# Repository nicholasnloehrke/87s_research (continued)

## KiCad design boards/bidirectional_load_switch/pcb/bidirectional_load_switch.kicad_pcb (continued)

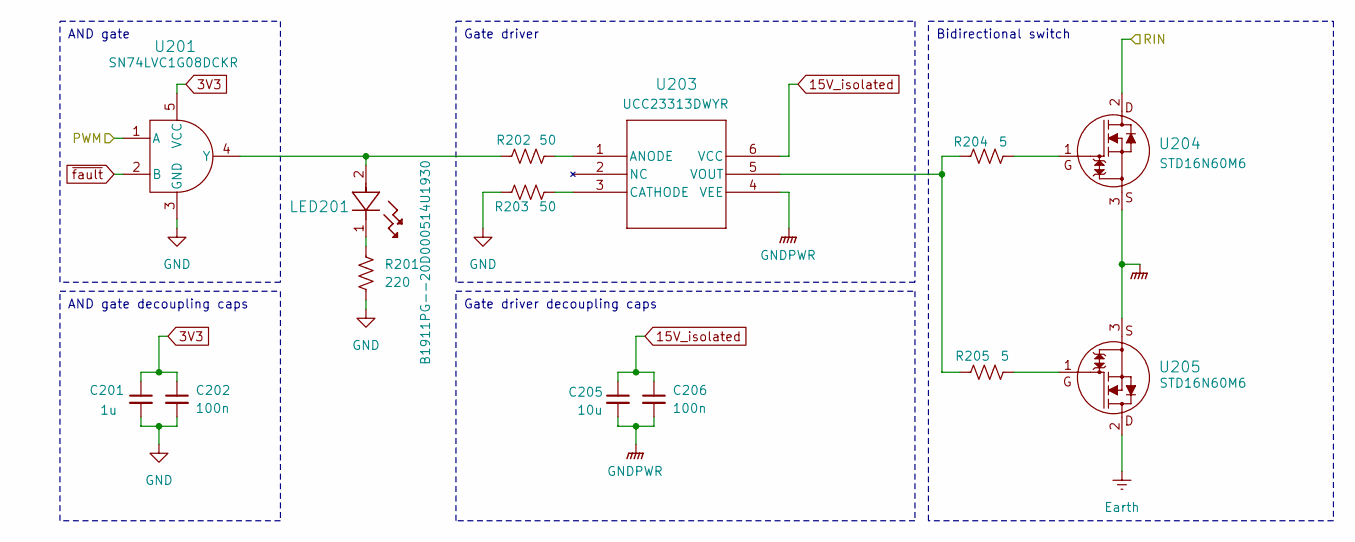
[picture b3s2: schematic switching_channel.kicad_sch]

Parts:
C201: 1u; C_0603_1608Metric
C202, C206: 100n; C_0603_1608Metric
C205: 10u; C_1206_3216Metric
LED201: LED_B1911PG--20D000514U1930_HVK; MPN B1911PG--20D000514U1930
R201: 220; R_0603_1608Metric
R202, R203: 50; R_0603_1608Metric
R204, R205: 5; R_0805_2012Metric
U201: DCK5; MPN SN74LVC1G08DCKR
U203: SOIC6_DWY_TEX; MPN UCC23313DWYR
U204, U205: DPAKTO-252_STM; MPN STD16N60M6

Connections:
3V3: C201.1, C202.1, U201.5 (VCC); also elsewhere on the board
15V_isolated: C205.1, C206.1, U203.6 (VCC); also elsewhere on the board
/Channel 1/RIN: U204.2; also elsewhere on the board
Earth: U205.2; also elsewhere on the board
GND: C201.2, C202.2, R201.2, R203.1, U201.3 (GND); also elsewhere on the board
GNDPWR: C205.2, C206.2, U203.4 (VEE), U204.3, U205.3; also elsewhere on the board
unnamed: LED201.1, R201.1
unnamed: R204.2, U204.1
unnamed: R205.2, U205.1
unnamed: LED201.2, R202.1, U201.4 (Y)
unnamed: R202.2, U203.1 (ANODE)
unnamed: R203.2, U203.3 (CATHODE)
unnamed: R204.1, R205.1, U203.5 (VOUT)
PWM1_in: U201.1 (A); also elsewhere on the board
~fault: U201.2 (B); also elsewhere on the board

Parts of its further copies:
C301, C401, C501, C601, C701, C801, C901: 1u; C_0603_1608Metric
C302, C306, C402, C406, C502, C506, C602, C606, C702, C706, C802, C806, C902, C906: 100n; C_0603_1608Metric
C305, C405, C505, C605, C705, C805, C905: 10u; C_1206_3216Metric
LED301, LED401, LED501, LED601, LED701, LED801, LED901: LED_B1911PG--20D000514U1930_HVK; MPN B1911PG--20D000514U1930
R301, R401, R501, R601, R701, R801, R901: 220; R_0603_1608Metric
R302, R303, R402, R403, R502, R503, R602, R603, R702, R703, R802, R803, R902, R903: 50; R_0603_1608Metric
R304, R305, R404, R405, R504, R505, R604, R605, R704, R705, R804, R805, R904, R905: 5; R_0805_2012Metric
U301, U401, U501, U601, U701, U801, U901: DCK5; MPN SN74LVC1G08DCKR
U303, U403, U503, U603, U703, U803, U903: SOIC6_DWY_TEX; MPN UCC23313DWYR
U304, U305, U404, U405, U504, U505, U604, U605, U704, U705, U804, U805, U904, U905: DPAKTO-252_STM; MPN STD16N60M6

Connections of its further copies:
3V3: C301.1, C302.1, C401.1, C402.1, C501.1, C502.1, C601.1, C602.1, C701.1, C702.1, C801.1, C802.1, C901.1, C902.1, U301.5 (VCC), U401.5 (VCC), U501.5 (VCC), U601.5 (VCC), U701.5 (VCC), U801.5 (VCC), U901.5 (VCC); also elsewhere on the board
15V_isolated: C305.1, C306.1, C405.1, C406.1, C505.1, C506.1, C605.1, C606.1, C705.1, C706.1, C805.1, C806.1, C905.1, C906.1, U303.6 (VCC), U403.6 (VCC), U503.6 (VCC), U603.6 (VCC), U703.6 (VCC), U803.6 (VCC), U903.6 (VCC); also elsewhere on the board
/Channel 2/RIN: U304.2; also elsewhere on the board
/Channel 3/RIN: U404.2; also elsewhere on the board
/Channel 4/RIN: U504.2; also elsewhere on the board
/Channel 5/RIN: U604.2; also elsewhere on the board
/Channel 6/RIN: U704.2; also elsewhere on the board
/Channel 7/RIN: U804.2; also elsewhere on the board
/Channel 8/RIN: U904.2; also elsewhere on the board
Earth: U305.2, U405.2, U505.2, U605.2, U705.2, U805.2, U905.2; also elsewhere on the board
GND: C301.2, C302.2, C401.2, C402.2, C501.2, C502.2, C601.2, C602.2, C701.2, C702.2, C801.2, C802.2, C901.2, C902.2, R301.2, R303.1, R401.2, R403.1, R501.2, R503.1, R601.2, R603.1, R701.2, R703.1, R801.2, R803.1, R901.2, R903.1, U301.3 (GND), U401.3 (GND), U501.3 (GND), U601.3 (GND), U701.3 (GND), U801.3 (GND), U901.3 (GND); also elsewhere on the board
GNDPWR: C305.2, C306.2, C405.2, C406.2, C505.2, C506.2, C605.2, C606.2, C705.2, C706.2, C805.2, C806.2, C905.2, C906.2, U303.4 (VEE), U304.3, U305.3, U403.4 (VEE), U404.3, U405.3, U503.4 (VEE), U504.3, U505.3, U603.4 (VEE), U604.3, U605.3, U703.4 (VEE), U704.3, U705.3, U803.4 (VEE), U804.3, U805.3, U903.4 (VEE), U904.3, U905.3; also elsewhere on the board
unnamed: LED301.1, R301.1
unnamed: LED401.1, R401.1
unnamed: LED501.1, R501.1
unnamed: LED601.1, R601.1
unnamed: LED701.1, R701.1
unnamed: LED801.1, R801.1
unnamed: LED901.1, R901.1
unnamed: R304.2, U304.1
unnamed: R305.2, U305.1
unnamed: R404.2, U404.1
unnamed: R405.2, U405.1
unnamed: R504.2, U504.1
unnamed: R505.2, U505.1
unnamed: R604.2, U604.1
unnamed: R605.2, U605.1
unnamed: R704.2, U704.1
unnamed: R705.2, U705.1
unnamed: R804.2, U804.1
unnamed: R805.2, U805.1
unnamed: R904.2, U904.1
unnamed: R905.2, U905.1
unnamed: LED301.2, R302.1, U301.4 (Y)
unnamed: R302.2, U303.1 (ANODE)
unnamed: R303.2, U303.3 (CATHODE)
unnamed: R304.1, R305.1, U303.5 (VOUT)
unnamed: LED401.2, R402.1, U401.4 (Y)
unnamed: R402.2, U403.1 (ANODE)
unnamed: R403.2, U403.3 (CATHODE)
unnamed: R404.1, R405.1, U403.5 (VOUT)
unnamed: LED501.2, R502.1, U501.4 (Y)
unnamed: R502.2, U503.1 (ANODE)
unnamed: R503.2, U503.3 (CATHODE)
unnamed: R504.1, R505.1, U503.5 (VOUT)
unnamed: LED601.2, R602.1, U601.4 (Y)
unnamed: R602.2, U603.1 (ANODE)
unnamed: R603.2, U603.3 (CATHODE)
unnamed: R604.1, R605.1, U603.5 (VOUT)
unnamed: LED701.2, R702.1, U701.4 (Y)
unnamed: R702.2, U703.1 (ANODE)
unnamed: R703.2, U703.3 (CATHODE)
unnamed: R704.1, R705.1, U703.5 (VOUT)
unnamed: LED801.2, R802.1, U801.4 (Y)
unnamed: R802.2, U803.1 (ANODE)
unnamed: R803.2, U803.3 (CATHODE)
unnamed: R804.1, R805.1, U803.5 (VOUT)
unnamed: LED901.2, R902.1, U901.4 (Y)
unnamed: R902.2, U903.1 (ANODE)
unnamed: R903.2, U903.3 (CATHODE)
unnamed: R904.1, R905.1, U903.5 (VOUT)
PWM2_in: U301.1 (A); also elsewhere on the board
PWM3_in: U401.1 (A); also elsewhere on the board
PWM4_in: U501.1 (A); also elsewhere on the board
PWM5_in: U601.1 (A); also elsewhere on the board
PWM6_in: U701.1 (A); also elsewhere on the board
PWM7_in: U801.1 (A); also elsewhere on the board
PWM8_in: U901.1 (A); also elsewhere on the board
~fault: U301.2 (B), U401.2 (B), U501.2 (B), U601.2 (B), U701.2 (B), U801.2 (B), U901.2 (B); also elsewhere on the board

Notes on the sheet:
Gate driver
Bidirectional switch
Gate driver decoupling caps
AND gate decoupling caps
AND gate

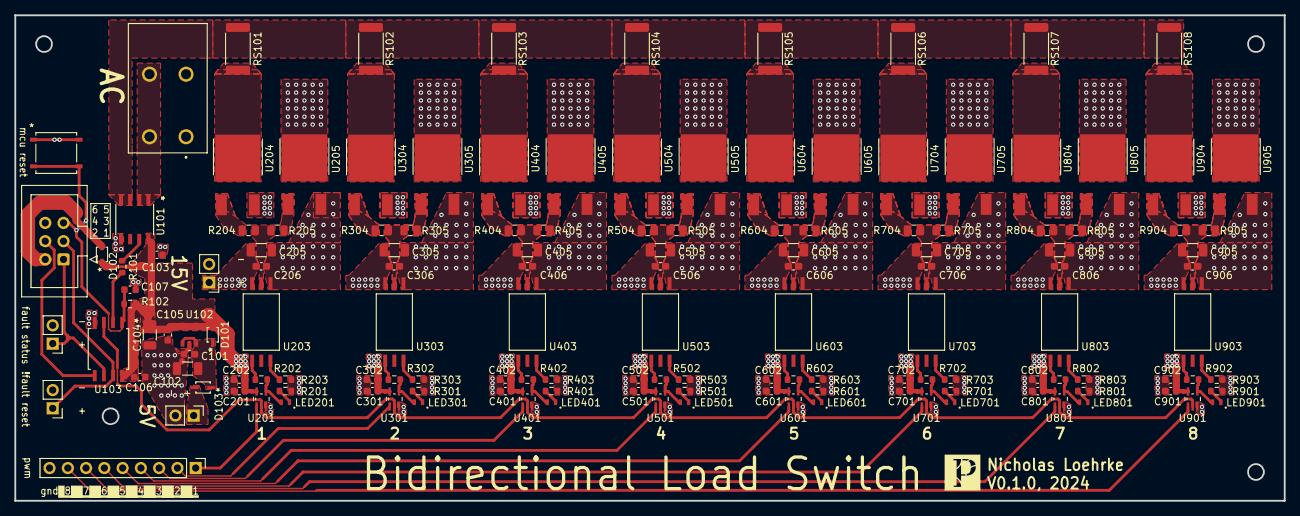
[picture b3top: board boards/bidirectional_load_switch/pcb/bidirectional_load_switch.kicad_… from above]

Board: 2 copper layers, 176.5 x 67.5 mm, 143 parts (0 on the bottom side), 89 nets.

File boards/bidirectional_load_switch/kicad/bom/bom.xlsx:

Reference | Value | Datasheet | Footprint | Qty | MPN
C101,C103,C105,C106,C107,C202,C206,C302,C306,C402,C406,C502,C506,C602,C606,C702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 | 100n | ~ | Capacitor_SMD:C_0603_1608Metric | 21
C102,C104,C205,C305,C405,C505,C605,C705,C805,C905 | 10u | ~ | Capacitor_SMD:C_1206_3216Metric | 10
C201,C301,C401,C501,C601,C701,C801,C901 | 1u | ~ | Capacitor_SMD:C_0603_1608Metric | 8
D101,D102 | ~ | https://toshiba.semicon-storage.com/info/CUS10S30_datasheet_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 | diode_CUS10S30_H3F:USC_TOS | 2 | CUS10S30_H3F
J101 | ~ | https://mm.digikey.com/Volume0/opasdata/d220001/medias/docus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 | spring_terminal_1017503:PHOENIX_1017503 | 1 | 1017503
J102,J104,J105,J106 | Conn_01x02_Socket | ~ | Connector_PinHeader_2.54mm:PinHeader_1x02_P2.54mm_Vertical | 4
J103 | Conn_01x09_Socket | ~ | Connector_PinHeader_2.54mm:PinHeader_1x09_P2.54mm_Vertical | 1
J107 | AVR-ISP-6 | ~ | Connector_IDC:IDC-Header_2x03_P2.54mm_Vertical | 1
LED201,LED301,LED401,LED501,LED601,LED701,LED801,LED901 | ~ | https://mm.digikey.com/Volume0/opasdata/d220001/medias/docus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 | led_B1911PG--20D000514U1930:LED_B1911PG--20D000514U1930_HVK | 8 | B1911PG--20D000514U1930
R101,R201,R301,R401,R501,R601,R701,R801,R901 | 220 | ~ | Resistor_SMD:R_0603_1608Metric | 9
R102 | 10k | ~ | Resistor_SMD:R_0603_1608Metric | 1
R202,R203,R302,R303,R402,R403,R502,R503,R602,R603,R702,R703,R802,R803,R902,R903 | 50 | ~ | Resistor_SMD:R_0603_1608Metric | 16
R204,R205,R304,R305,R404,R405,R504,R505,R604,R605,R704,R705,R804,R805,R904,R905 | 5 | ~ | Resistor_SMD:R_0805_2012Metric | 16
RS101 | 1 | ~ | Resistor_SMD:R_2512_6332Metric | 1
RS102 | 3.9 | ~ | Resistor_SMD:R_2512_6332Metric | 1
RS103 | 15 | ~ | Resistor_SMD:R_2512_6332Metric | 1
RS104 | 47 | ~ | Resistor_SMD:R_2512_6332Metric | 1
RS105 | 200 | ~ | Resistor_SMD:R_2512_6332Metric | 1
RS106 | 680 | ~ | Resistor_SMD:R_2512_6332Metric | 1
RS107 | 2700 | ~ | Resistor_SMD:R_2512_6332Metric | 1
RS108 | 10000 | ~ | Resistor_SMD:R_2512_6332Metric | 1
SW101 | ~ | https://www.ckswitches.com/media/2780/pts526.pdf | switch_PTS526_SK15_SMTR2_LFS:SMT_FS | 1 | PTS526 SK15 SMTR2 LFS
U101 | ~ | https://www.ti.com/general/docs/suppproductinfo.tsp?distId=1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 | current_sensor_TMCS1101A3BQDR:SOIC8_D_TEX | 1 | TMCS1101A3BQDRQ1
U102 | ~ | https://www.ti.com/general/docs/suppproductinfo.tsp?distId=1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 | ldo_TLV75733PDBVR:DBV0005A_L | 1 | TLV75733PDBVR
U103 | ~ | https://ww1.microchip.com/downloads/en/DeviceDoc/Atmel-2586-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 | mcu_ATTINY85_20SU:8S2_ATM | 1 | ATTINY85-20SU
U201,U301,U401,U501,U601,U701,U801,U901 | ~ | https://www.ti.com/general/docs/suppproductinfo.tsp?distId=1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 | and_gate_SN74LVC1G08DCKR:DCK5 | 8 | SN74LVC1G08DCKR
U203,U303,U403,U503,U603,U703,U803,U903 | ~ | https://www.ti.com/general/docs/suppproductinfo.tsp?distId=1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 | gate_driver_UCC23313DWYR:SOIC6_DWY_TEX | 8 | UCC23313DWYR
U204,U205,U304,U305,U404,U405,U504,U505,U604,U605,U704,U705,U804,U805,U904,U905 | ~ | https://www.st.com/resource/en/datasheet/std16n60m6.pdf | mosfet_STD16N60M6:DPAKTO-252_STM | 16 | STD16N60M6

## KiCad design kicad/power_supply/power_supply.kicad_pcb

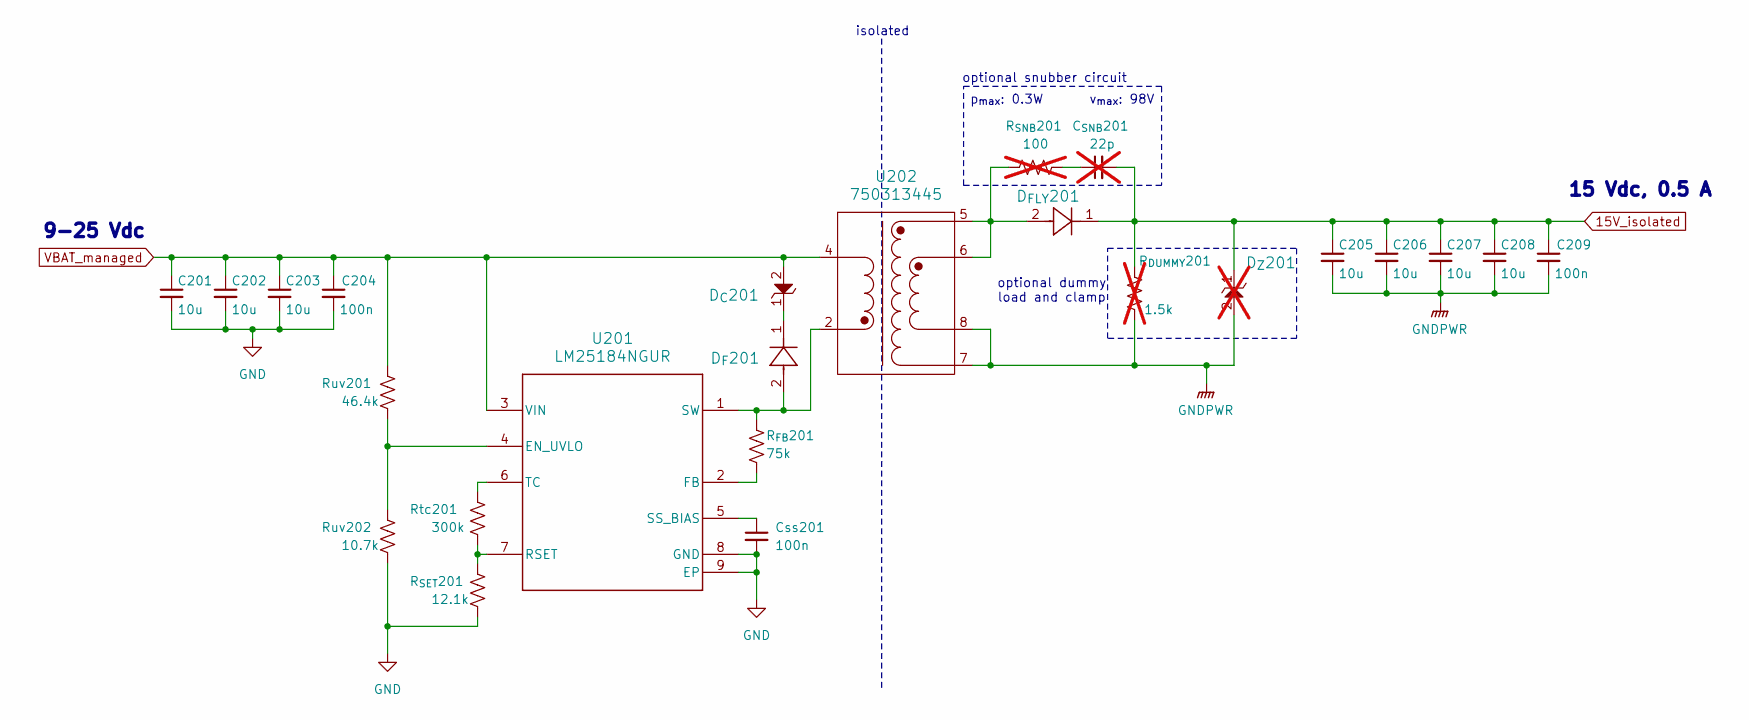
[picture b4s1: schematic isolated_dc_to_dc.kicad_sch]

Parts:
C201, C202, C203, C205, C206, C207, C208: 10u; C_1206_3216Metric
C204, C209: 100n; C_0402_1005Metric
C_{SNB}201: 22p; C_0402_1005Metric; not fitted
Css201: 100n; C_0402_1005Metric
D_{C}201: PDZVTR9.1B; DIO_PDZVTFT_ROM
D_{FLY}201: SK510A-LTP; SMADO-214AC_LEAD-FRAME_MCC
D_{F}201: SK510A-LTP; SMADO-214AC_LEAD-FRAME_MCC
D_{Z}201: PDZVTR9.1B; DIO_PDZVTFT_ROM; not fitted
R_{DUMMY}201: 1.5k; R_0402_1005Metric; not fitted
R_{FB}201: 75k; R_0402_1005Metric
R_{SET}201: 12.1k; R_0402_1005Metric
R_{SNB}201: 100; R_0402_1005Metric; not fitted
Rtc201: 300k; R_0402_1005Metric
Ruv201: 46.4k; R_0402_1005Metric
Ruv202: 10.7k; R_0402_1005Metric
U201: LM25184NGUR; NGU0008C-IPC_A
U202: 750313445; SOIC_13445_WRE

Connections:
15V_isolated: C205.1, C206.1, C207.1, C208.1, C209.1, C_{SNB}201.2, D_{FLY}201.1, D_{Z}201.1, R_{DUMMY}201.2
GND: C201.2, C202.2, C203.2, C204.2, Css201.2, R_{SET}201.2, Ruv202.2, U201.8 (GND), U201.9 (EP)
GNDPWR: C205.2, C206.2, C207.2, C208.2, C209.2, D_{Z}201.2, R_{DUMMY}201.1, U202.7, U202.8
unnamed: C_{SNB}201.1, R_{SNB}201.2
unnamed: D_{C}201.1, D_{F}201.1
unnamed: D_{FLY}201.2, R_{SNB}201.1, U202.5, U202.6
unnamed: Ruv201.2, Ruv202.1, U201.4 (EN_UVLO)
unnamed: R_{FB}201.2, U201.2 (FB)
unnamed: R_{SET}201.1, Rtc201.2, U201.7 (RSET)
unnamed: Css201.1, U201.5 (SS_BIAS)
unnamed: D_{F}201.2, R_{FB}201.1, U201.1 (SW), U202.2
unnamed: Rtc201.1, U201.6 (TC)
VBAT_managed: C201.1, C202.1, C203.1, C204.1, D_{C}201.2, Ruv201.1, U201.3 (VIN), U202.4

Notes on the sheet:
optional snubber circuit
optional dummy load and clamp
9-25 Vdc
isolated
p_{max}: 0.3W
15 Vdc, 0.5 A
v_{max}: 98V

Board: 2 copper layers, 24 parts (0 on the bottom side), 13 nets, no tracks yet.

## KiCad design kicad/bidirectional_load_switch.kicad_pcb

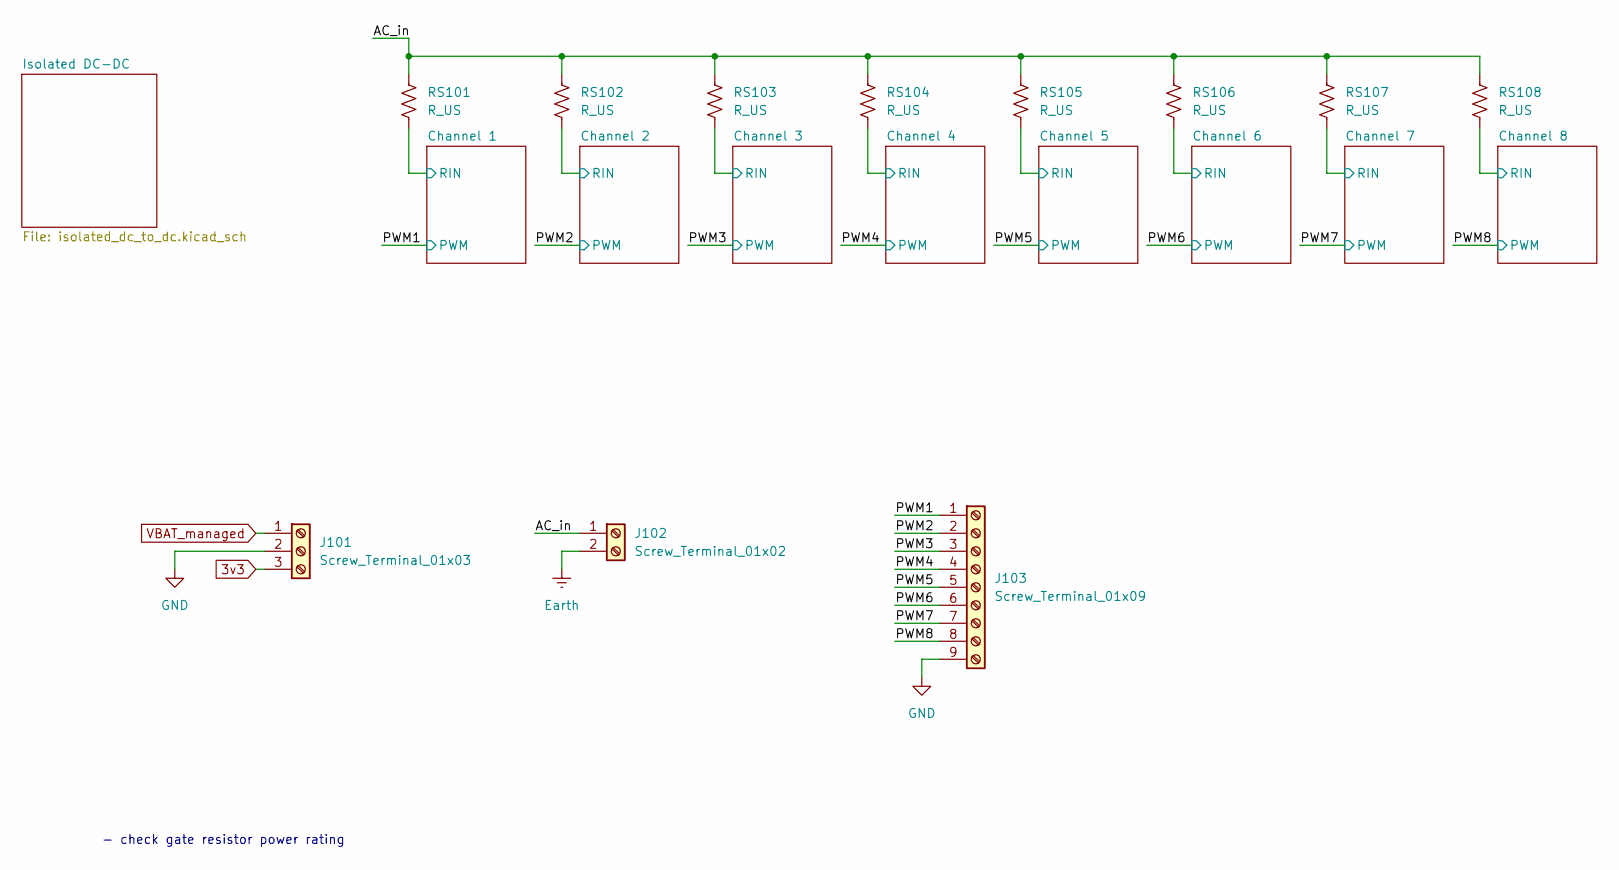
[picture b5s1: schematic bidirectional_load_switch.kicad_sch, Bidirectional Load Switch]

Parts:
J101: Screw_Terminal_01x03; TerminalBlock_Xinya_XY308-2.54-3P_1x03_P2.54mm_Horizontal
J102: Screw_Terminal_01x02; TerminalBlock_Xinya_XY308-2.54-2P_1x02_P2.54mm_Horizontal
J103: Screw_Terminal_01x09; TerminalBlock_Xinya_XY308-2.54-9P_1x09_P2.54mm_Horizontal
RS101, RS102, RS103, RS104, RS105, RS106, RS107, RS108: R_US; R_1206_3216Metric_Pad1.30x1.75mm_HandSolder

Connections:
3v3: J101.3; also elsewhere on the board
/AC_in: J102.1, RS101.1, RS102.1, RS103.1, RS104.1, RS105.1, RS106.1, RS107.1, RS108.1
/Channel 1/RIN: RS101.2; also elsewhere on the board
/Channel 2/RIN: RS102.2; also elsewhere on the board
/Channel 3/RIN: RS103.2; also elsewhere on the board
/Channel 4/RIN: RS104.2; also elsewhere on the board
/Channel 5/RIN: RS105.2; also elsewhere on the board
/Channel 6/RIN: RS106.2; also elsewhere on the board
/Channel 7/RIN: RS107.2; also elsewhere on the board
/Channel 8/RIN: RS108.2; also elsewhere on the board
/PWM1: J103.1; also elsewhere on the board
/PWM2: J103.2; also elsewhere on the board
/PWM3: J103.3; also elsewhere on the board
/PWM4: J103.4; also elsewhere on the board
/PWM5: J103.5; also elsewhere on the board
/PWM6: J103.6; also elsewhere on the board
/PWM7: J103.7; also elsewhere on the board
/PWM8: J103.8; also elsewhere on the board
Earth: J102.2; also elsewhere on the board
GND: J101.2, J103.9; also elsewhere on the board
VBAT_managed: J101.1; also elsewhere on the board

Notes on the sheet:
- check gate resistor power rating

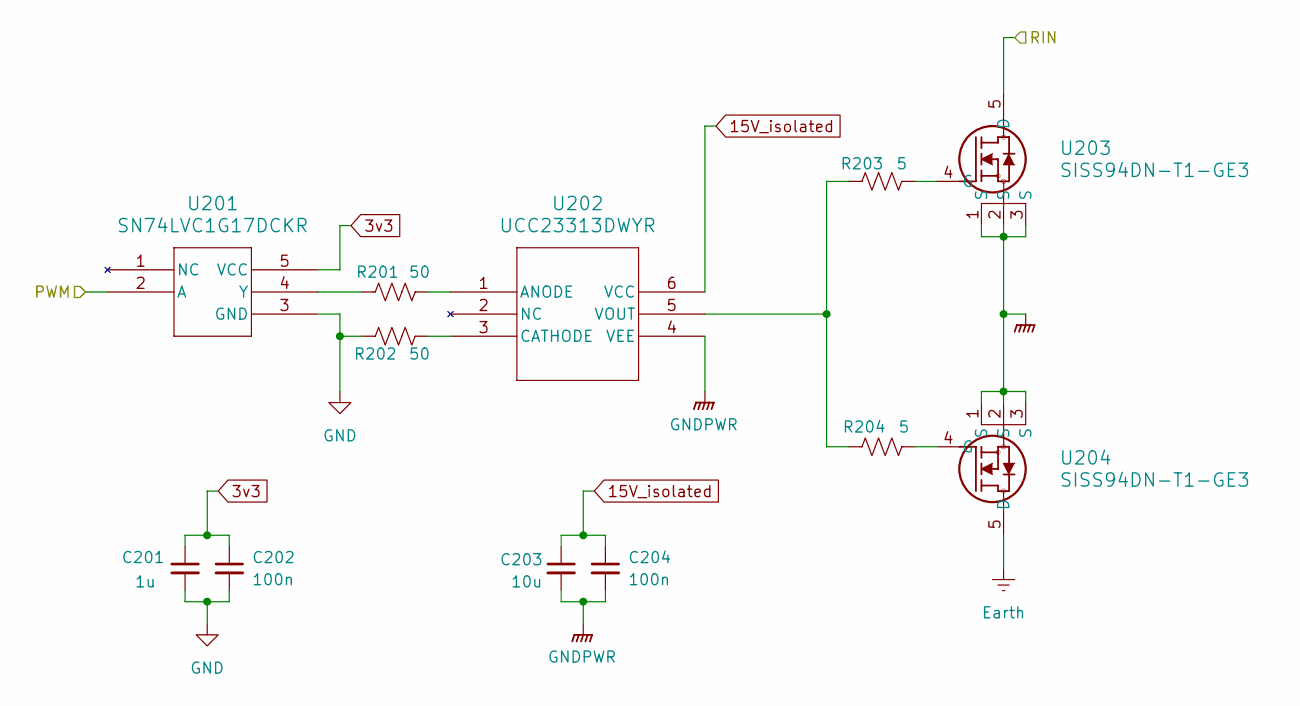
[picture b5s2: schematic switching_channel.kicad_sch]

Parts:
C201: 1u; C_0603_1608Metric
C202: 100n; C_0402_1005Metric
C203: 10u; C_1206_3216Metric
C204: 100n; C_0805_2012Metric
R201, R202: 50; R_0402_1005Metric_Pad0.72x0.64mm_HandSolder
R203, R204: 5; R_0603_1608Metric_Pad0.98x0.95mm_HandSolder
U201: SN74LVC1G17DCKR; DCK5
U202: UCC23313DWYR; SOIC6_DWY_TEX
U203, U204: SISS94DN-T1-GE3; MOSFET_3DN-T1-GE3_VIS

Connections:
3v3: C201.1, C202.1, U201.5 (VCC); also elsewhere on the board
15V_isolated: C203.1, C204.1, U202.6 (VCC); also elsewhere on the board
/Channel 1/RIN: U203.5 (D); also elsewhere on the board
/PWM1: U201.2 (A); also elsewhere on the board
Earth: U204.5 (D); also elsewhere on the board
GND: C201.2, C202.2, R202.1, U201.3 (GND); also elsewhere on the board
GNDPWR: C203.2, C204.2, U202.4 (VEE), U203.1 (S), U203.2 (S), U203.3 (S), U204.1 (S), U204.2 (S), U204.3 (S); also elsewhere on the board
unnamed: R201.1, U201.4 (Y)
unnamed: R201.2, U202.1 (ANODE)
unnamed: R202.2, U202.3 (CATHODE)
unnamed: R203.1, R204.1, U202.5 (VOUT)
unnamed: R203.2, U203.4 (G)
unnamed: R204.2, U204.4 (G)

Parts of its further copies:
C301, C401, C501, C601, C701, C801, C901: 1u; C_0603_1608Metric
C302, C402, C502, C602, C702, C802, C902: 100n; C_0402_1005Metric
C303, C403, C503, C603, C703, C803, C903: 10u; C_1206_3216Metric
C304, C404, C504, C604, C704, C804, C904: 100n; C_0805_2012Metric
R301, R302, R401, R402, R501, R502, R601, R602, R701, R702, R801, R802, R901, R902: 50; R_0402_1005Metric_Pad0.72x0.64mm_HandSolder
R303, R304, R403, R404, R503, R504, R603, R604, R703, R704, R803, R804, R903, R904: 5; R_0603_1608Metric_Pad0.98x0.95mm_HandSolder
U301, U401, U501, U601, U701, U801, U901: SN74LVC1G17DCKR; DCK5
U302, U402, U502, U602, U702, U802, U902: UCC23313DWYR; SOIC6_DWY_TEX
U303, U304, U403, U404, U503, U504, U603, U604, U703, U704, U803, U804, U903, U904: SISS94DN-T1-GE3; MOSFET_3DN-T1-GE3_VIS

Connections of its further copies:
3v3: C301.1, C302.1, C401.1, C402.1, C501.1, C502.1, C601.1, C602.1, C701.1, C702.1, C801.1, C802.1, C901.1, C902.1, U301.5 (VCC), U401.5 (VCC), U501.5 (VCC), U601.5 (VCC), U701.5 (VCC), U801.5 (VCC), U901.5 (VCC); also elsewhere on the board
15V_isolated: C303.1, C304.1, C403.1, C404.1, C503.1, C504.1, C603.1, C604.1, C703.1, C704.1, C803.1, C804.1, C903.1, C904.1, U302.6 (VCC), U402.6 (VCC), U502.6 (VCC), U602.6 (VCC), U702.6 (VCC), U802.6 (VCC), U902.6 (VCC); also elsewhere on the board
/Channel 2/RIN: U303.5 (D); also elsewhere on the board
/Channel 3/RIN: U403.5 (D); also elsewhere on the board
/Channel 4/RIN: U503.5 (D); also elsewhere on the board
/Channel 5/RIN: U603.5 (D); also elsewhere on the board
/Channel 6/RIN: U703.5 (D); also elsewhere on the board
/Channel 7/RIN: U803.5 (D); also elsewhere on the board
/Channel 8/RIN: U903.5 (D); also elsewhere on the board
/PWM2: U301.2 (A); also elsewhere on the board
/PWM3: U401.2 (A); also elsewhere on the board
/PWM4: U501.2 (A); also elsewhere on the board
/PWM5: U601.2 (A); also elsewhere on the board
/PWM6: U701.2 (A); also elsewhere on the board
/PWM7: U801.2 (A); also elsewhere on the board
/PWM8: U901.2 (A); also elsewhere on the board
Earth: U304.5 (D), U404.5 (D), U504.5 (D), U604.5 (D), U704.5 (D), U804.5 (D), U904.5 (D); also elsewhere on the board
GND: C301.2, C302.2, C401.2, C402.2, C501.2, C502.2, C601.2, C602.2, C701.2, C702.2, C801.2, C802.2, C901.2, C902.2, R302.1, R402.1, R502.1, R602.1, R702.1, R802.1, R902.1, U301.3 (GND), U401.3 (GND), U501.3 (GND), U601.3 (GND), U701.3 (GND), U801.3 (GND), U901.3 (GND); also elsewhere on the board
GNDPWR: C303.2, C304.2, C403.2, C404.2, C503.2, C504.2, C603.2, C604.2, C703.2, C704.2, C803.2, C804.2, C903.2, C904.2, U302.4 (VEE), U303.1 (S), U303.2 (S), U303.3 (S), U304.1 (S), U304.2 (S), U304.3 (S), U402.4 (VEE), U403.1 (S), U403.2 (S), U403.3 (S), U404.1 (S), U404.2 (S), U404.3 (S), U502.4 (VEE), U503.1 (S), U503.2 (S), U503.3 (S), U504.1 (S), U504.2 (S), U504.3 (S), U602.4 (VEE), U603.1 (S), U603.2 (S), U603.3 (S), U604.1 (S), U604.2 (S), U604.3 (S), U702.4 (VEE), U703.1 (S), U703.2 (S), U703.3 (S), U704.1 (S), U704.2 (S), U704.3 (S), U802.4 (VEE), U803.1 (S), U803.2 (S), U803.3 (S), U804.1 (S), U804.2 (S), U804.3 (S), U902.4 (VEE), U903.1 (S), U903.2 (S), U903.3 (S), U904.1 (S), U904.2 (S), U904.3 (S); also elsewhere on the board
unnamed: R301.1, U301.4 (Y)
unnamed: R301.2, U302.1 (ANODE)
unnamed: R302.2, U302.3 (CATHODE)
unnamed: R303.1, R304.1, U302.5 (VOUT)
unnamed: R303.2, U303.4 (G)
unnamed: R304.2, U304.4 (G)
unnamed: R401.1, U401.4 (Y)
unnamed: R401.2, U402.1 (ANODE)
unnamed: R402.2, U402.3 (CATHODE)
unnamed: R403.1, R404.1, U402.5 (VOUT)
unnamed: R403.2, U403.4 (G)
unnamed: R404.2, U404.4 (G)
unnamed: R501.1, U501.4 (Y)
unnamed: R501.2, U502.1 (ANODE)
unnamed: R502.2, U502.3 (CATHODE)
unnamed: R503.1, R504.1, U502.5 (VOUT)
unnamed: R503.2, U503.4 (G)
unnamed: R504.2, U504.4 (G)
unnamed: R601.1, U601.4 (Y)
unnamed: R601.2, U602.1 (ANODE)
unnamed: R602.2, U602.3 (CATHODE)
unnamed: R603.1, R604.1, U602.5 (VOUT)
unnamed: R603.2, U603.4 (G)
unnamed: R604.2, U604.4 (G)
unnamed: R701.1, U701.4 (Y)
unnamed: R701.2, U702.1 (ANODE)
unnamed: R702.2, U702.3 (CATHODE)
unnamed: R703.1, R704.1, U702.5 (VOUT)
unnamed: R703.2, U703.4 (G)
unnamed: R704.2, U704.4 (G)
unnamed: R801.1, U801.4 (Y)
unnamed: R801.2, U802.1 (ANODE)
unnamed: R802.2, U802.3 (CATHODE)
unnamed: R803.1, R804.1, U802.5 (VOUT)
unnamed: R803.2, U803.4 (G)
unnamed: R804.2, U804.4 (G)
unnamed 67: R901.1, U901.4 (Y); also elsewhere on the board
unnamed: R901.2, U902.1 (ANODE)
unnamed: R902.2, U902.3 (CATHODE)
unnamed: R903.1, R904.1, U902.5 (VOUT)
unnamed: R903.2, U903.4 (G)
unnamed: R904.2, U904.4 (G)

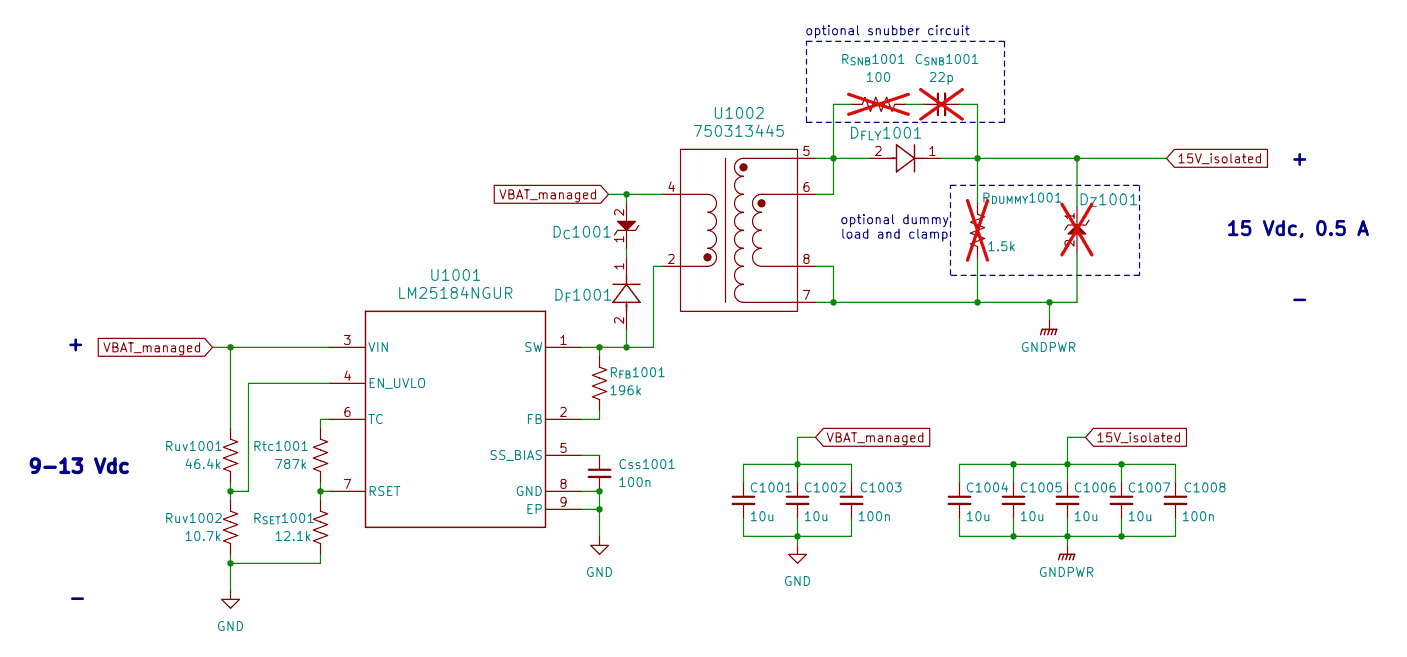
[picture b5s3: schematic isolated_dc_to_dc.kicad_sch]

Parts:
C1001, C1002, C1004, C1005, C1006, C1007: 10u; C_1206_3216Metric
C1003, C1008: 100n; C_0402_1005Metric
C_{SNB}1001: 22p; C_0402_1005Metric; not fitted
Css1001: 100n; C_0402_1005Metric
D_{C}1001: PDZVTR9.1B; DIO_PDZVTFT_ROM
D_{FLY}1001: SK510A-LTP; SMADO-214AC_LEAD-FRAME_MCC
D_{F}1001: SK510A-LTP; SMADO-214AC_LEAD-FRAME_MCC
D_{Z}1001: PDZVTR9.1B; DIO_PDZVTFT_ROM; not fitted
R_{DUMMY}1001: 1.5k; R_0402_1005Metric; not fitted
R_{FB}1001: 196k; R_0402_1005Metric
R_{SET}1001: 12.1k; R_0402_1005Metric
R_{SNB}1001: 100; R_0402_1005Metric; not fitted
Rtc1001: 787k; R_0402_1005Metric
Ruv1001: 46.4k; R_0402_1005Metric
Ruv1002: 10.7k; R_0402_1005Metric
U1001: LM25184NGUR; NGU0008C-IPC_A
U1002: 750313445; SOIC_13445_WRE

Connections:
15V_isolated: C1004.1, C1005.1, C1006.1, C1007.1, C1008.1, C_{SNB}1001.2, D_{FLY}1001.1, D_{Z}1001.1, R_{DUMMY}1001.2; also elsewhere on the board
GND: C1001.2, C1002.2, C1003.2, Css1001.2, R_{SET}1001.2, Ruv1002.2, U1001.8 (GND), U1001.9 (EP); also elsewhere on the board
GNDPWR: C1004.2, C1005.2, C1006.2, C1007.2, C1008.2, D_{Z}1001.2, R_{DUMMY}1001.1, U1002.7, U1002.8; also elsewhere on the board
unnamed: C_{SNB}1001.1, R_{SNB}1001.2
unnamed: D_{C}1001.1, D_{F}1001.1
unnamed: D_{FLY}1001.2, R_{SNB}1001.1, U1002.5, U1002.6
unnamed: Ruv1001.2, Ruv1002.1, U1001.4 (EN_UVLO)
unnamed: R_{FB}1001.2, U1001.2 (FB)
unnamed: R_{SET}1001.1, Rtc1001.2, U1001.7 (RSET)
unnamed: Css1001.1, U1001.5 (SS_BIAS)
unnamed: D_{F}1001.2, R_{FB}1001.1, U1001.1 (SW), U1002.2
unnamed: Rtc1001.1, U1001.6 (TC)
VBAT_managed: C1001.1, C1002.1, C1003.1, D_{C}1001.2, Ruv1001.1, U1001.3 (VIN), U1002.4; also elsewhere on the board

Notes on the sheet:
optional snubber circuit
optional dummy load and clamp
15 Vdc, 0.5 A
9-13 Vdc

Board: 2 copper layers, 131 parts (0 on the bottom side), 80 nets, no tracks yet.

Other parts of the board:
U901#2: SN74LVC1G17DCKR; DCK5

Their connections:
3v3: U901#2.5 (VCC); also elsewhere on the board
/PWM8: U901#2.2 (A); also elsewhere on the board
GND: U901#2.3 (GND); also elsewhere on the board
unnamed 67: U901#2.4 (Y); also elsewhere on the board

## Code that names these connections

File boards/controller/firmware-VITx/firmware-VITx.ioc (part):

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Mcu.Name=STM32U575VITx
Mcu.Package=LQFP100
Mcu.UserName=STM32U575VITx
PA0.GPIOParameters=GPIO_Label
PA0.GPIO_Label=BLS_CH4
PA0.Signal=S_TIM5_CH1
PA1.GPIOParameters=GPIO_Label
PA1.GPIO_Label=BLS_CH3
PA1.Signal=S_TIM5_CH2
PA11.GPIOParameters=GPIO_Label
PA11.GPIO_Label=USB_DM
PA11.Mode=Device_Only
PA11.Signal=USB_OTG_FS_DM
PA12.GPIOParameters=GPIO_Label
PA12.GPIO_Label=USB_DP
PA12.Mode=Device_Only
PA12.Signal=USB_OTG_FS_DP
PA13\ (JTMS/SWDIO).GPIOParameters=GPIO_Label
PA13\ (JTMS/SWDIO).GPIO_Label=SWDIO
PA13\ (JTMS/SWDIO).Mode=Serial_Wire
PA13\ (JTMS/SWDIO).Signal=DEBUG_JTMS-SWDIO
PA14\ (JTCK/SWCLK).GPIOParameters=GPIO_Label
PA14\ (JTCK/SWCLK).GPIO_Label=SWCLK
PA14\ (JTCK/SWCLK).Mode=Serial_Wire
PA14\ (JTCK/SWCLK).Signal=DEBUG_JTCK-SWCLK
PA15\ (JTDI).GPIOParameters=GPIO_Label
PA15\ (JTDI).GPIO_Label=USB_CC1
PA15\ (JTDI).Mode=Sink_AllSignals
PA15\ (JTDI).Signal=UCPD1_CC1
PA2.GPIOParameters=GPIO_Label
PA2.GPIO_Label=BLS_CH2
PA2.Signal=S_TIM2_CH3
PA3.GPIOParameters=GPIO_Label
PA3.GPIO_Label=BLS_CH1
PA3.Signal=S_TIM2_CH4
PA4.GPIOParameters=GPIO_Label
PA4.GPIO_Label=CHG_QONn
PA4.Signal=GPIO_Output
PA5.GPIOParameters=GPIO_Label
PA5.GPIO_Label=ENC_2An
PA5.Signal=S_TIM2_CH1
PA6.GPIOParameters=GPIO_Label
PA6.GPIO_Label=VBAT_SENSE_EN
PA6.Signal=GPIO_Output
PA7.GPIOParameters=GPIO_Label
PA7.GPIO_Label=VBAT_SENSE
PA7.Mode=IN12-Single-Ended
PA7.Signal=ADC1_IN12
PB10.GPIOParameters=GPIO_Label
PB10.GPIO_Label=TP_RSTn
PB10.Signal=GPIO_Output
PB12.GPIOParameters=GPIO_Label
PB12.GPIO_Label=TP_INTn
PB12.Signal=GPXTI12
PB13.GPIOParameters=GPIO_Label
PB13.GPIO_Label=TP_SCL
PB13.Mode=I2C
PB13.Signal=I2C2_SCL
PB14.GPIOParameters=GPIO_Label
PB14.GPIO_Label=TP_SDA
PB14.Mode=I2C
PB14.Signal=I2C2_SDA
PB15.GPIOParameters=GPIO_Label
PB15.GPIO_Label=USB_CC2
PB15.Mode=Sink_AllSignals
PB15.Signal=UCPD1_CC2
PB3\ (JTDO/TRACESWO).GPIOParameters=GPIO_Label
PB3\ (JTDO/TRACESWO).GPIO_Label=ENC_2Bn
PB3\ (JTDO/TRACESWO).Signal=S_TIM2_CH2
PB4\ (NJTRST).GPIOParameters=GPIO_Label
PB4\ (NJTRST).GPIO_Label=ENC_2SWn
PB4\ (NJTRST).Signal=GPXTI4
PB6.GPIOParameters=GPIO_Label
PB6.GPIO_Label=EEPROM_SCL
PB6.Mode=I2C
PB6.Signal=I2C1_SCL
PB7.GPIOParameters=GPIO_Label
PB7.GPIO_Label=EEPROM_SDA
PB7.Mode=I2C
PB7.Signal=I2C1_SDA
PC0.GPIOParameters=GPIO_Label
PC0.GPIO_Label=CHG_SCL
PC0.Mode=I2C
PC0.Signal=I2C3_SCL
PC1.GPIOParameters=GPIO_Label
PC1.GPIO_Label=CHG_SDA
PC1.Mode=I2C
PC1.Signal=I2C3_SDA
PC11.GPIOParameters=GPIO_Label
PC11.GPIO_Label=FLYBACK_EN
PC11.Signal=GPIO_Output
PC12.GPIOParameters=GPIO_Label
PC12.GPIO_Label=BLS_RSTn
PC12.Signal=GPIO_Output
PC2.GPIOParameters=GPIO_Label
PC2.GPIO_Label=CHG_INTn
PC2.Signal=GPXTI2
PC3.GPIOParameters=GPIO_Label
PC3.GPIO_Label=CHG_ENn
PC3.Signal=GPIO_Output
PC7.GPIOParameters=GPIO_Label
PC7.GPIO_Label=TCP_DBn
PC7.Signal=GPIO_Output
PC8.GPIOParameters=GPIO_Label
PC8.GPIO_Label=TCP_FLTn
PC8.Signal=GPXTI8
PC9.GPIOParameters=GPIO_Label
PC9.GPIO_Label=TCP_VCC
PC9.Signal=GPIO_Output
PD0.GPIOParameters=GPIO_Label
PD0.GPIO_Label=BLS_ENn
PD0.Signal=GPIO_Output
PD1.GPIOParameters=GPIO_Label
PD1.GPIO_Label=BLS_SCLK
PD1.Mode=Full_Duplex_Master
PD1.Signal=SPI2_SCK
PD10.GPIOParameters=GPIO_Label
PD10.GPIO_Label=PWR_SW_SENSEn
PD10.Signal=GPXTI10
PD11.GPIOParameters=GPIO_Label
PD11.GPIO_Label=ENC_3SWn
PD11.Signal=GPXTI11
PD12.GPIOParameters=GPIO_Label
PD12.GPIO_Label=ENC_3An
PD12.Signal=S_TIM4_CH1
PD13.GPIOParameters=GPIO_Label
PD13.GPIO_Label=ENC_3Bn
PD13.Signal=S_TIM4_CH2
PD14.GPIOParameters=GPIO_Label
PD14.GPIO_Label=BLS_CH7
PD14.Signal=S_TIM4_CH3
PD15.GPIOParameters=GPIO_Label
PD15.GPIO_Label=BLS_CH8
PD15.Signal=S_TIM4_CH4
PD3.GPIOParameters=GPIO_Label
PD3.GPIO_Label=BLS_MISO
PD3.Mode=Full_Duplex_Master
PD3.Signal=SPI2_MISO
PD4.GPIOParameters=GPIO_Label
PD4.GPIO_Label=BLS_MOSI
PD4.Mode=Full_Duplex_Master
PD4.Signal=SPI2_MOSI
PD5.Mode=Asynchronous
PD5.Signal=USART2_TX
PD6.Mode=Asynchronous
PD6.Signal=USART2_RX
PD9.GPIOParameters=GPIO_Label
PD9.GPIO_Label=PWR_SW_LATCH
PD9.Signal=GPIO_Output
PE1.GPIOParameters=GPIO_Label
PE1.GPIO_Label=ENC_1SWn
PE1.Signal=GPXTI1
PE10.GPIOParameters=GPIO_Label
PE10.GPIO_Label=LCD_DC
PE10.Signal=GPIO_Output
PE11.GPIOParameters=GPIO_Label
PE11.GPIO_Label=LCD_RSTn
PE11.Signal=GPIO_Output
PE12.GPIOParameters=GPIO_Label
PE12.GPIO_Label=LCD_BL
PE12.Signal=GPIO_Output
PE13.GPIOParameters=GPIO_Label
PE13.GPIO_Label=DISP_SCLK
PE13.Mode=Full_Duplex_Master
PE13.Signal=SPI1_SCK
PE14.GPIOParameters=GPIO_Label
PE14.GPIO_Label=DISP_MISO
PE14.Mode=Full_Duplex_Master
PE14.Signal=SPI1_MISO
PE15.GPIOParameters=GPIO_Label
PE15.GPIO_Label=DISP_MOSI
PE15.Mode=Full_Duplex_Master
PE15.Signal=SPI1_MOSI
PE3.GPIOParameters=GPIO_PuPd,GPIO_Label
PE3.GPIO_Label=ENC_1An
PE3.GPIO_PuPd=GPIO_NOPULL
PE3.Signal=S_TIM3_CH1
PE4.GPIOParameters=GPIO_Label
PE4.GPIO_Label=ENC_1Bn
PE4.Signal=S_TIM3_CH2
PE5.GPIOParameters=GPIO_Label
PE5.GPIO_Label=BLS_CH6
PE5.Signal=S_TIM3_CH3
PE6.GPIOParameters=GPIO_Label
PE6.GPIO_Label=BLS_CH5
PE6.Signal=S_TIM3_CH4
PE7.GPIOParameters=GPIO_Label
PE7.GPIO_Label=DISP_ENn
PE7.Signal=GPIO_Output
PE8.GPIOParameters=GPIO_Label
PE8.GPIO_Label=SD_CSn
PE8.Signal=GPIO_Output
PE9.GPIOParameters=GPIO_Label
PE9.GPIO_Label=LCD_CSn
PE9.Signal=GPIO_Output
PH0-OSC_IN\ (PH0).Mode=HSE-External-Oscillator
PH0-OSC_IN\ (PH0).Signal=RCC_OSC_IN
PH1-OSC_OUT\ (PH1).Mode=HSE-External-Oscillator
PH1-OSC_OUT\ (PH1).Signal=RCC_OSC_OUT
RCC.HSE_VALUE=16000000
RCC.SYSCLKFreq_VALUE=128000000
RCC.SYSCLKSource=RCC_SYSCLKSOURCE_PLLCLK
board=custom

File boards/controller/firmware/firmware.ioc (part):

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Mcu.Name=STM32U575RITx
Mcu.Package=LQFP64
Mcu.UserName=STM32U575RITx
PA0.GPIOParameters=GPIO_Label
PA0.GPIO_Label=BLS_CH1
PA0.Signal=S_TIM2_CH1
PA1.GPIOParameters=GPIO_Label
PA1.GPIO_Label=BLS_CH2
PA1.Signal=S_TIM2_CH2
PA10.GPIOParameters=GPIO_Label
PA10.GPIO_Label=USB_DB
PA10.Signal=GPIO_Input
PA11.Mode=Device_Only
PA11.Signal=USB_OTG_FS_DM
PA12.Mode=Device_Only
PA12.Signal=USB_OTG_FS_DP
PA13\ (JTMS/SWDIO).Mode=Serial_Wire
PA13\ (JTMS/SWDIO).Signal=DEBUG_JTMS-SWDIO
PA14\ (JTCK/SWCLK).Mode=Serial_Wire
PA14\ (JTCK/SWCLK).Signal=DEBUG_JTCK-SWCLK
PA15\ (JTDI).Mode=Sink_AllSignals
PA15\ (JTDI).Signal=UCPD1_CC1
PA2.GPIOParameters=GPIO_Label
PA2.GPIO_Label=BLS_CH3
PA2.Signal=S_TIM2_CH3
PA3.GPIOParameters=GPIO_Label
PA3.GPIO_Label=BLS_CH4
PA3.Signal=S_TIM2_CH4
PA4.GPIOParameters=GPIO_Label
PA4.GPIO_Label=BLS_STATUS
PA4.Signal=GPXTI4
PA5.GPIOParameters=GPIO_Label
PA5.GPIO_Label=BLS_FAULT_RESET
PA5.Signal=GPIO_Output
PA6.GPIOParameters=GPIO_Label
PA6.GPIO_Label=BLS_CH5
PA6.Signal=S_TIM3_CH1
PA7.GPIOParameters=GPIO_Label
PA7.GPIO_Label=BLS_CH6
PA7.Signal=S_TIM3_CH2
PA8.GPIOParameters=GPIO_Label
PA8.GPIO_Label=VBUS_DETECT
PA8.Signal=GPIO_Input
PA9.GPIOParameters=GPIO_Label
PA9.GPIO_Label=USB_FLT
PA9.Signal=GPIO_Input
PB0.GPIOParameters=GPIO_Label
PB0.GPIO_Label=BLS_CH7
PB0.Signal=S_TIM3_CH3
PB1.GPIOParameters=GPIO_Label
PB1.GPIO_Label=BLS_CH8
PB1.Signal=S_TIM3_CH4
PB10.GPIOParameters=GPIO_Label
PB10.GPIO_Label=ENC1_B
PB10.Signal=GPXTI10
PB12.GPIOParameters=GPIO_Label
PB12.GPIO_Label=ENC1_BTN
PB12.Signal=GPXTI12
PB13.GPIOParameters=GPIO_Label
PB13.GPIO_Label=ENC2_A
PB13.Signal=GPXTI13
PB14.GPIOParameters=GPIO_Label
PB14.GPIO_Label=ENC2_B
PB14.Signal=GPXTI14
PB15.Mode=Sink_AllSignals
PB15.Signal=UCPD1_CC2
PB2.GPIOParameters=GPIO_Label
PB2.GPIO_Label=ENC1_A
PB2.Signal=GPXTI2
PB3\ (JTDO/TRACESWO).GPIOParameters=GPIO_Label
PB3\ (JTDO/TRACESWO).GPIO_Label=LCD_SCK
PB3\ (JTDO/TRACESWO).Mode=Full_Duplex_Master
PB3\ (JTDO/TRACESWO).Signal=SPI1_SCK
PB4\ (NJTRST).GPIOParameters=GPIO_Label
PB4\ (NJTRST).GPIO_Label=LCD_MISO
PB4\ (NJTRST).Mode=Full_Duplex_Master
PB4\ (NJTRST).Signal=SPI1_MISO
PB5.GPIOParameters=GPIO_Label
PB5.GPIO_Label=LCD_MOSI
PB5.Mode=Full_Duplex_Master
PB5.Signal=SPI1_MOSI
PB6.GPIOParameters=GPIO_Label
PB6.GPIO_Label=SD_CS
PB6.Signal=GPIO_Output
PB7.GPIOParameters=GPIO_Label
PB7.GPIO_Label=TP_RST
PB7.Signal=GPIO_Output
PB8.GPIOParameters=GPIO_Label,GPIO_Pu
PB8.GPIO_Label=TP_ADC_SCL
PB8.GPIO_Pu=GPIO_NOPULL
PB8.Mode=I2C
PB8.Signal=I2C1_SCL
PB9.GPIOParameters=GPIO_Label
PB9.GPIO_Label=TP_ADC_SDA
PB9.Mode=I2C
PB9.Signal=I2C1_SDA
PC0.GPIOParameters=GPIO_Label
PC0.GPIO_Label=CHG_ACOK
PC0.Signal=GPXTI0
PC1.GPIOParameters=GPIO_Label
PC1.GPIO_Label=CHG_STAT
PC1.Signal=GPXTI1
PC10.GPIOParameters=GPIO_Label
PC10.GPIO_Label=LCD_BL
PC10.Signal=GPIO_Output
PC11.GPIOParameters=GPIO_Label
PC11.GPIO_Label=LCD_RST
PC11.Signal=GPIO_Output
PC12.GPIOParameters=GPIO_Label
PC12.GPIO_Label=LCD_DC
PC12.Signal=GPIO_Output
PC13.GPIOParameters=GPIO_Label
PC13.GPIO_Label=LED1
PC13.Signal=GPIO_Output
PC14-OSC32_IN\ (PC14).GPIOParameters=GPIO_Label
PC14-OSC32_IN\ (PC14).GPIO_Label=PWR_BTN
PC14-OSC32_IN\ (PC14).Signal=GPIO_Input
PC15-OSC32_OUT\ (PC15).GPIOParameters=GPIO_Label
PC15-OSC32_OUT\ (PC15).GPIO_Label=TP_INT
PC15-OSC32_OUT\ (PC15).Signal=GPXTI15
PC2.GPIOParameters=GPIO_Label
PC2.GPIO_Label=CHG_EN
PC2.Signal=GPIO_Output
PC3.GPIOParameters=GPIO_Label
PC3.GPIO_Label=PWR_LATCH
PC3.Signal=GPIO_Output
PC4.Mode=Asynchronous
PC4.Signal=USART3_TX
PC5.Mode=Asynchronous
PC5.Signal=USART3_RX
PC6.GPIOParameters=GPIO_Label
PC6.GPIO_Label=ENC2_BTN
PC6.Signal=GPXTI6
PC7.GPIOParameters=GPIO_Label
PC7.GPIO_Label=ENC3_A
PC7.Signal=GPXTI7
PC8.GPIOParameters=GPIO_Label
PC8.GPIO_Label=ENC3_B
PC8.Signal=GPXTI8
PC9.GPIOParameters=GPIO_Label
PC9.GPIO_Label=ENC3_BTN
PC9.Signal=GPXTI9
PD2.GPIOParameters=GPIO_Label
PD2.GPIO_Label=LCD_CS
PD2.Signal=GPIO_Output
PH0-OSC_IN\ (PH0).Mode=HSE-External-Oscillator
PH0-OSC_IN\ (PH0).Signal=RCC_OSC_IN
PH1-OSC_OUT\ (PH1).Mode=HSE-External-Oscillator
PH1-OSC_OUT\ (PH1).Signal=RCC_OSC_OUT
PH3-BOOT0.GPIOParameters=GPIO_Label
PH3-BOOT0.GPIO_Label=BOOT0
PH3-BOOT0.Signal=GPXTI3
RCC.HSE_VALUE=16000000
RCC.SYSCLKFreq_VALUE=160000000
RCC.SYSCLKSource=RCC_SYSCLKSOURCE_PLLCLK
board=custom
